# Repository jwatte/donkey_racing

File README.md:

Tools to help train the donkey car models.

`ip_beacon`: a program that broadcasts the presence of a node on a network for easy finding.
It can also browse for said nodes on the local network.

`teensy_rc_control`: a sketch for the Arduino IDE with the Teensyduino package installed, to 
control a gas-and-steering robot based on received RC commands and communication with a USB 
host (such as a Raspberry Pi or NVIDIA Jetson.)

`mktraining`: generates a synthetic set of images similar to what a rpi camera might capture.
horizontal FOV 60 degrees; resolution 320x240; random confetti on the floor for each image.
Libraries needed to build: GLFW and GLEW.

`blur`: blur a PNG image based on a mask given in another PNG image.

`teensy_32_carrier`: KiCad design files for the servo and receiver I/O board for the Teensy 3.2
microcontroller. Known flaws in revision 1.0:
  - Doesn't connect to Raspbery Pi "hat" port
  - Doesn't have enough I/Os to read BLDC motor sensors

All of these tools also want "stb" to be a checkout of github.com/nothings/stb as a peer 
to these directories.

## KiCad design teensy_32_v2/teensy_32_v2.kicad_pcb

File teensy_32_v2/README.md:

Teensy Hat notes

User manual: https://docs.google.com/document/d/1TIZRwT1liuum8qoM7WJbi-JH8VMrMioTwOWIgUCem8s/edit?usp=sharing

  * Version 1 (4 copies) commit number:  328d241c250156cd1f0e025fa5ad50edf611e549
  * Version 2 (8 copies) commit number:  3ad820124f71cb1f2d3cb137cd7d391197ac48be

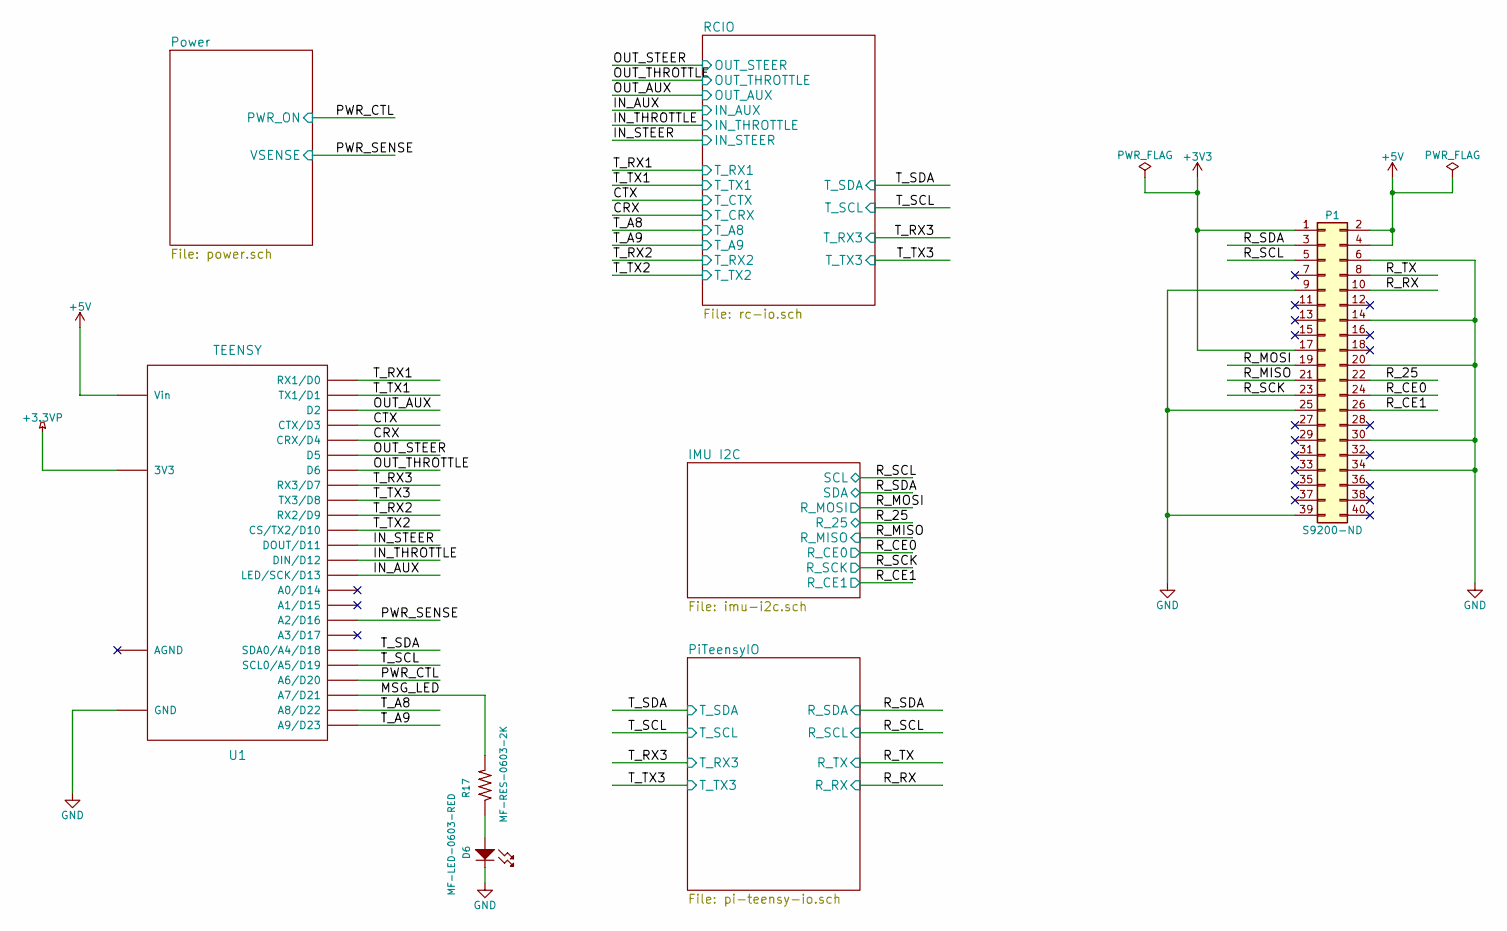
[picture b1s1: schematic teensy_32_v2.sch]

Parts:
D6: MF-LED-0603-RED; MF_LEDs-LED0603
P1: S9200-ND; RPI_BOTTOM_NOLABELS
R17: MF-RES-0603-2K; MF_Passives-R0603
U1: TEENSY; TEENSY_3

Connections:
+3.3VP: U1.26 (3V3)
+3V3: P1.1, P1.17; also elsewhere on the board
+5V: P1.2, P1.4, U1.28 (Vin); also elsewhere on the board
/CRX: U1.6 (CRX/D4); also elsewhere on the board
/CTX: U1.5 (CTX/D3); also elsewhere on the board
/IN_AUX: U1.15 (LED/SCK/D13); also elsewhere on the board
/IN_STEER: U1.13 (DOUT/D11); also elsewhere on the board
/IN_THROTTLE: U1.14 (DIN/D12); also elsewhere on the board
/MSG_LED: R17.2, U1.23 (A7/D21)
/OUT_AUX: U1.4 (D2); also elsewhere on the board
/OUT_STEER: U1.7 (D5); also elsewhere on the board
/OUT_THROTTLE: U1.8 (D6); also elsewhere on the board
/PWR_CTL: U1.22 (A6/D20); also elsewhere on the board
/PWR_SENSE: U1.18 (A2/D16); also elsewhere on the board
/R_25: P1.22; also elsewhere on the board
/R_CE0: P1.24; also elsewhere on the board
/R_CE1: P1.26; also elsewhere on the board
/R_MISO: P1.21; also elsewhere on the board
/R_MOSI: P1.19; also elsewhere on the board
/R_RX: P1.10; also elsewhere on the board
/R_SCK: P1.23; also elsewhere on the board
/R_SCL: P1.5; also elsewhere on the board
/R_SDA: P1.3; also elsewhere on the board
/R_TX: P1.8; also elsewhere on the board
/T_A8: U1.24 (A8/D22); also elsewhere on the board
/T_A9: U1.25 (A9/D23); also elsewhere on the board
/T_RX1: U1.2 (RX1/D0); also elsewhere on the board
/T_RX2: U1.11 (RX2/D9); also elsewhere on the board
/T_RX3: U1.9 (RX3/D7); also elsewhere on the board
/T_SCL: U1.21 (SCL0/A5/D19); also elsewhere on the board
/T_SDA: U1.20 (SDA0/A4/D18); also elsewhere on the board
/T_TX1: U1.3 (TX1/D1); also elsewhere on the board
/T_TX2: U1.12 (CS/TX2/D10); also elsewhere on the board
/T_TX3: U1.10 (TX3/D8); also elsewhere on the board
GND: D6.CATH (CATHODE), P1.6, P1.9, P1.14, P1.20, P1.25, P1.30, P1.34, P1.39, U1.1 (GND); also elsewhere on the board
unnamed: D6.ANOD (ANODE), R17.1

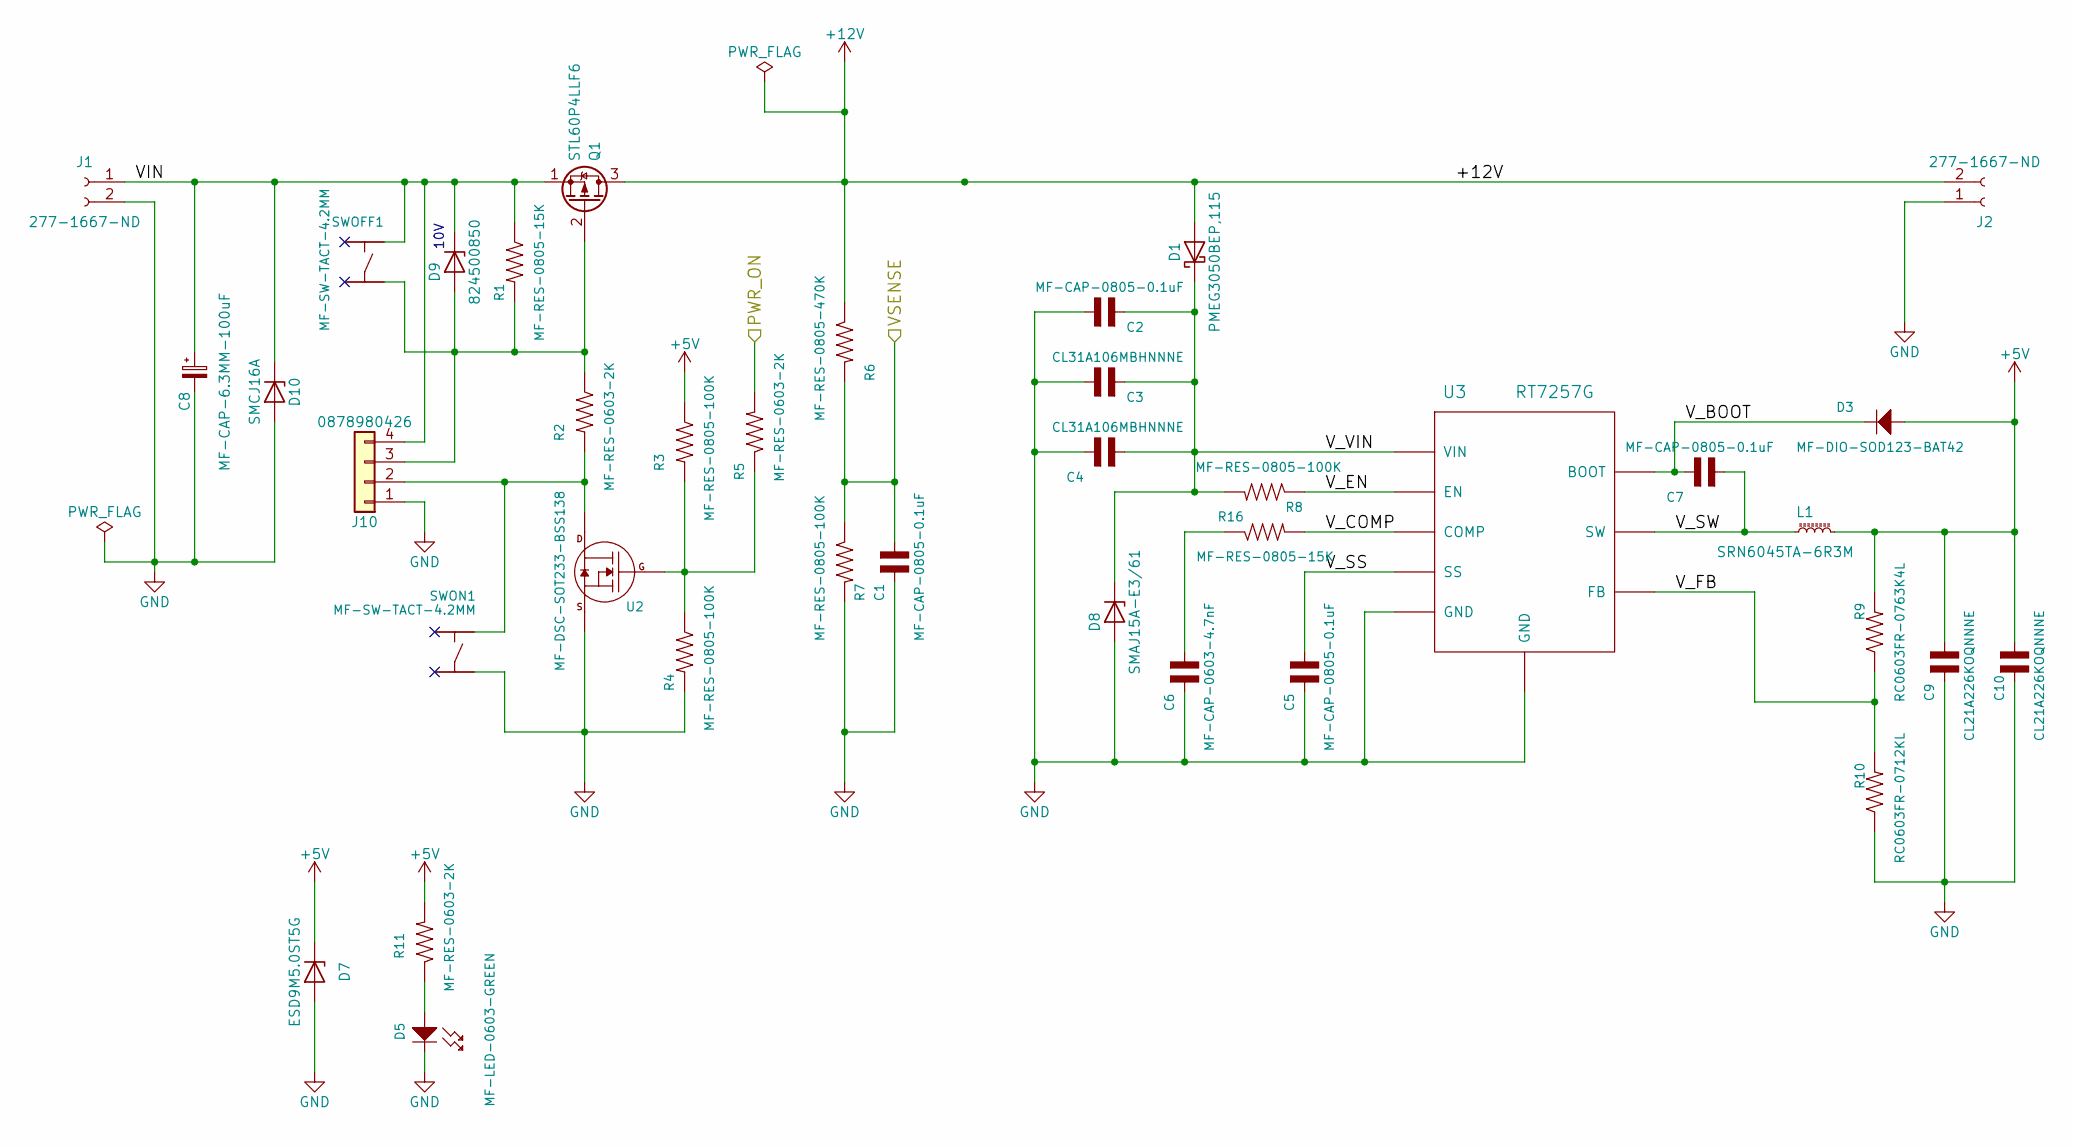
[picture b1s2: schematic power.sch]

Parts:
C1, C2, C5, C7: MF-CAP-0805-0.1uF; MF_Passives-C0805
C3, C4: CL31A106MBHNNNE; MF_Passives-C1206
C6: MF-CAP-0603-4.7nF; MF_Passives-C0603
C8: MF-CAP-6.3MM-100uF; MF_Passives-CP6.3MM
C9, C10: CL21A226KOQNNNE; MF_Passives-C0805
D1: PMEG3050BEP,115; SOD-128
D3: MF-DIO-SOD123-BAT42; MF_Discrete_Semiconductor-SOD-123
D5: MF-LED-0603-GREEN; MF_LEDs-LED0603
D7: ESD9M5.0ST5G; SOD-923
D8: SMAJ15A-E3/61; D_SMA_Standard
D9: 824500850; D_SMA_Standard
D10: SMCJ16A; D_SMC_Standard
J1, J2: 277-1667-ND; PhoenixContact_MCV-G_02x5.08mm_Vertical
J10: 0878980426; MF_Connectors-PTH_2.54MM_01X04
L1: SRN6045TA-6R3M; SRN6045TA
Q1: STL60P4LLF6; POWERFLAT_5x6
R1, R16: MF-RES-0805-15K; MF_Passives-R0805
R2, R5, R11: MF-RES-0603-2K; MF_Passives-R0603
R3, R4, R7, R8: MF-RES-0805-100K; MF_Passives-R0805
R6: MF-RES-0805-470K; MF_Passives-R0805
R9: RC0603FR-0763K4L; MF_Passives-R0603
R10: RC0603FR-0712KL; MF_Passives-R0603
SWOFF1: MF-SW-TACT-4.2MM; MF_Switches-TACT4.2MM
SWON1: MF-SW-TACT-4.2MM; MF_Switches-TACT4.2MM
U2: MF-DSC-SOT233-BSS138; MF_Discrete_Semiconductor-SOT-23-3
U3: RT7257G; DS7257G

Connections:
+5V: C9.1, C10.1, D3.ANOD (ANODE), D7.1, L1.2, R3.1, R9.2, R11.2; also elsewhere on the board
+12V: D1.2 (A), J2.2, Q1.3 (D), R6.1; also elsewhere on the board
/PWR_CTL: R5.2; also elsewhere on the board
/PWR_SENSE: C1.1, R6.2, R7.1; also elsewhere on the board
/Power/VIN: C8.1, D9.1, D10.1 (K), J1.1, J10.4, Q1.1 (S), R1.1, SWOFF1.1
/Power/V_BOOT: C7.1, D3.CATH (CATHODE), U3.1 (BOOT)
/Power/V_COMP: R16.2, U3.6 (COMP)
/Power/V_EN: R8.1, U3.7 (EN)
/Power/V_FB: R9.1, R10.2, U3.5 (FB)
/Power/V_SS: C5.1, U3.8 (SS)
/Power/V_SW: C7.2, L1.1, U3.3 (SW)
/Power/V_VIN: C2.2, C3.2, C4.2, D1.1 (K), D8.1, R8.2, U3.2 (VIN)
GND: C1.2, C2.1, C3.1, C4.1, C5.2, C6.2, C8.2, C9.2, C10.2, D5.CATH (CATHODE), D7.2, D8.2, D10.2 (A), J1.2, J2.1, J10.1, R4.2, R7.2, R10.1, SWON1.3, U2.2 (SOURCE), U3.4 (GND), U3.9 (GND); also elsewhere on the board
unnamed: C6.1, R16.1
unnamed: D5.ANOD (ANODE), R11.1
unnamed: D9.2, J10.3, Q1.2 (G), R1.2, R2.1, SWOFF1.3
unnamed: J10.2, R2.2, SWON1.1, U2.3 (DRAIN)
unnamed: R3.2, R4.1, R5.1, U2.1 (GATE)

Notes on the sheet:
10V

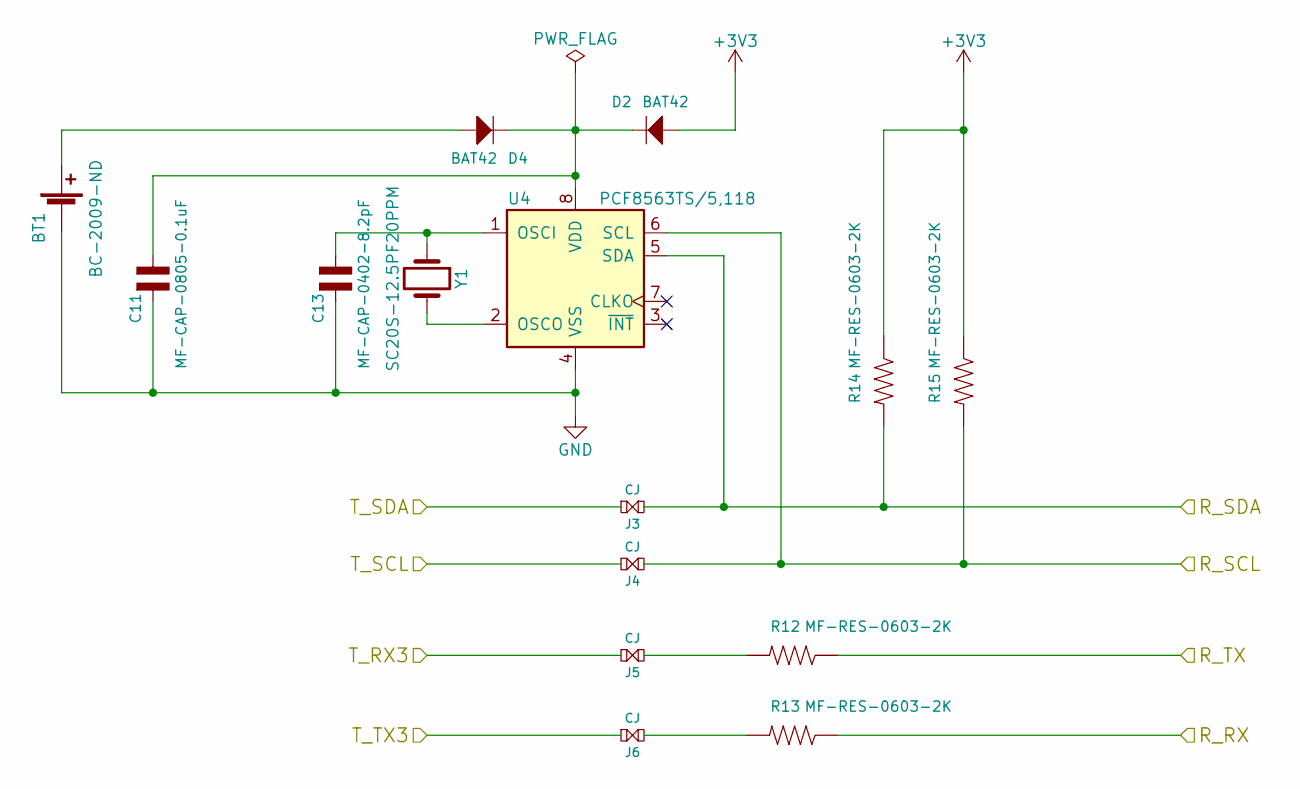
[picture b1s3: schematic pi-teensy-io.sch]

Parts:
BT1: BC-2009-ND
C11: MF-CAP-0805-0.1uF; MF_Passives-C0805
C13: MF-CAP-0402-8.2pF; MF_Passives-C0402
D2, D4: BAT42; MF_Discrete_Semiconductor-SOD-123
J3, J4, J5, J6: CJ; CJ-2
R12, R13, R14, R15: MF-RES-0603-2K; MF_Passives-R0603
U4: PCF8563TS/5,118; TSSOP-8_3x3mm_Pitch0.65mm
Y1: SC20S-12.5PF20PPM; SC-20S

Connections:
+3V3: D2.ANOD (ANODE), R14.1, R15.1; also elsewhere on the board
/R_RX: R13.1; also elsewhere on the board
/R_SCL: J4.2, R15.2, U4.6 (SCL); also elsewhere on the board
/R_SDA: J3.2, R14.2, U4.5 (SDA); also elsewhere on the board
/R_TX: R12.1; also elsewhere on the board
/T_RX3: J5.1; also elsewhere on the board
/T_SCL: J4.1; also elsewhere on the board
/T_SDA: J3.1; also elsewhere on the board
/T_TX3: J6.1; also elsewhere on the board
GND: BT1.2 (-), C11.2, C13.2, U4.4 (VSS); also elsewhere on the board
unnamed: BT1.1 (+), D4.ANOD (ANODE)
unnamed: C11.1, D2.CATH (CATHODE), D4.CATH (CATHODE), U4.8 (VDD)
unnamed: C13.1, U4.1 (OSCI), Y1.1
unnamed: J5.2, R12.2
unnamed: J6.2, R13.2
unnamed: U4.2 (OSCO), Y1.2

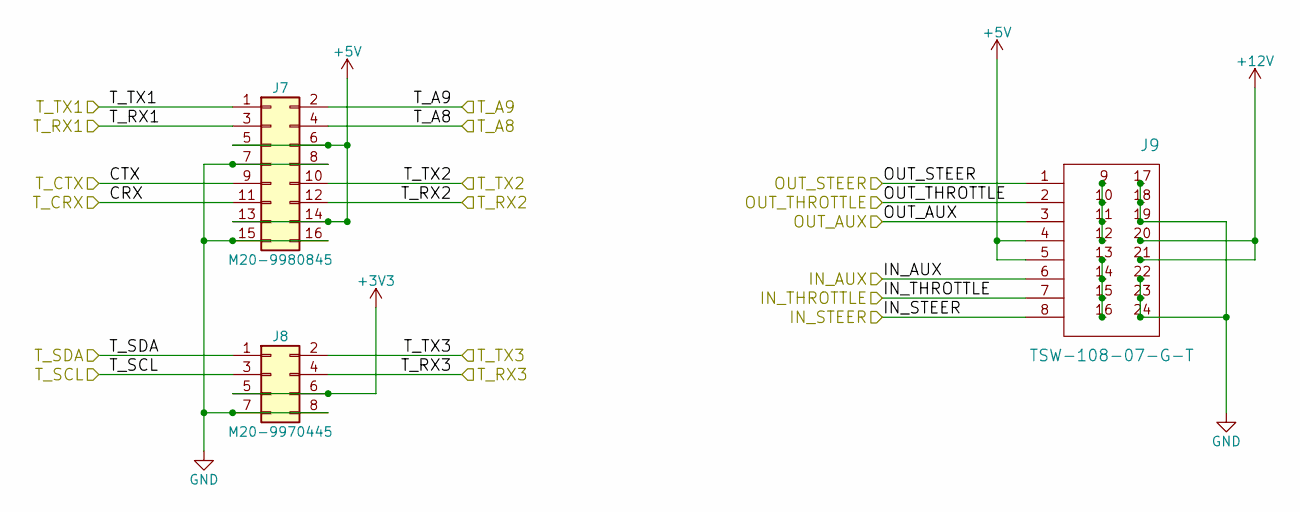
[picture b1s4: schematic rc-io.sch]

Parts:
J7: M20-9980845; Pin_Header_Straight_2x08_Pitch2.54mm
J8: M20-9970445; Pin_Header_Straight_2x04_Pitch2.54mm
J9: TSW-108-07-G-T; CONN_03x08

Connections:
+3V3: J8.5, J8.6; also elsewhere on the board
+5V: J7.5, J7.6, J7.13, J7.14, J9.4, J9.5; also elsewhere on the board
+12V: J9.20, J9.21; also elsewhere on the board
/CRX: J7.11; also elsewhere on the board
/CTX: J7.9; also elsewhere on the board
/IN_AUX: J9.6; also elsewhere on the board
/IN_STEER: J9.8; also elsewhere on the board
/IN_THROTTLE: J9.7; also elsewhere on the board
/OUT_AUX: J9.3; also elsewhere on the board
/OUT_STEER: J9.1; also elsewhere on the board
/OUT_THROTTLE: J9.2; also elsewhere on the board
/T_A8: J7.4; also elsewhere on the board
/T_A9: J7.2; also elsewhere on the board
/T_RX1: J7.3; also elsewhere on the board
/T_RX2: J7.12; also elsewhere on the board
/T_RX3: J8.4; also elsewhere on the board
/T_SCL: J8.3; also elsewhere on the board
/T_SDA: J8.1; also elsewhere on the board
/T_TX1: J7.1; also elsewhere on the board
/T_TX2: J7.10; also elsewhere on the board
/T_TX3: J8.2; also elsewhere on the board
GND: J7.7, J7.8, J7.15, J7.16, J8.7, J8.8, J9.17, J9.18, J9.19, J9.22, J9.23, J9.24; also elsewhere on the board
unnamed: J9.9, J9.10, J9.11, J9.12
unnamed: J9.13, J9.14, J9.15, J9.16

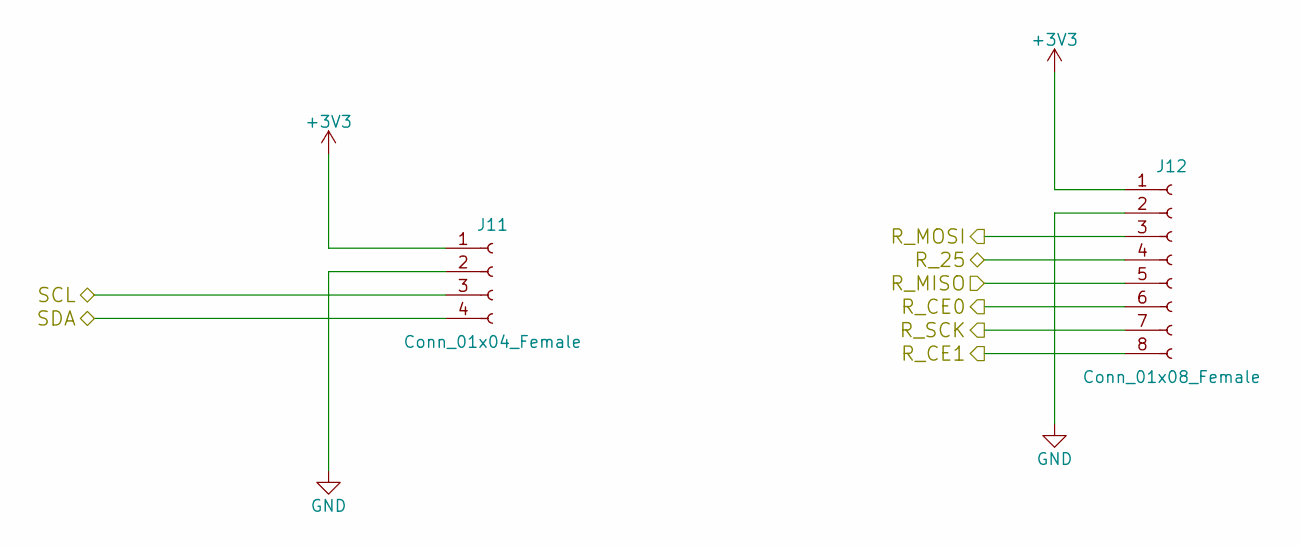
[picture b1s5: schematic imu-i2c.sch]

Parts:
J11: Conn_01x04_Female; Pin_Header_Straight_1x04_Pitch2.54mm
J12: Conn_01x08_Female; Pin_Header_Straight_1x08_Pitch2.54mm

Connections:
+3V3: J11.1, J12.1; also elsewhere on the board
/R_25: J12.4; also elsewhere on the board
/R_CE0: J12.6; also elsewhere on the board
/R_CE1: J12.8; also elsewhere on the board
/R_MISO: J12.5; also elsewhere on the board
/R_MOSI: J12.3; also elsewhere on the board
/R_SCK: J12.7; also elsewhere on the board
/R_SCL: J11.3; also elsewhere on the board
/R_SDA: J11.4; also elsewhere on the board
GND: J11.2, J12.2; also elsewhere on the board

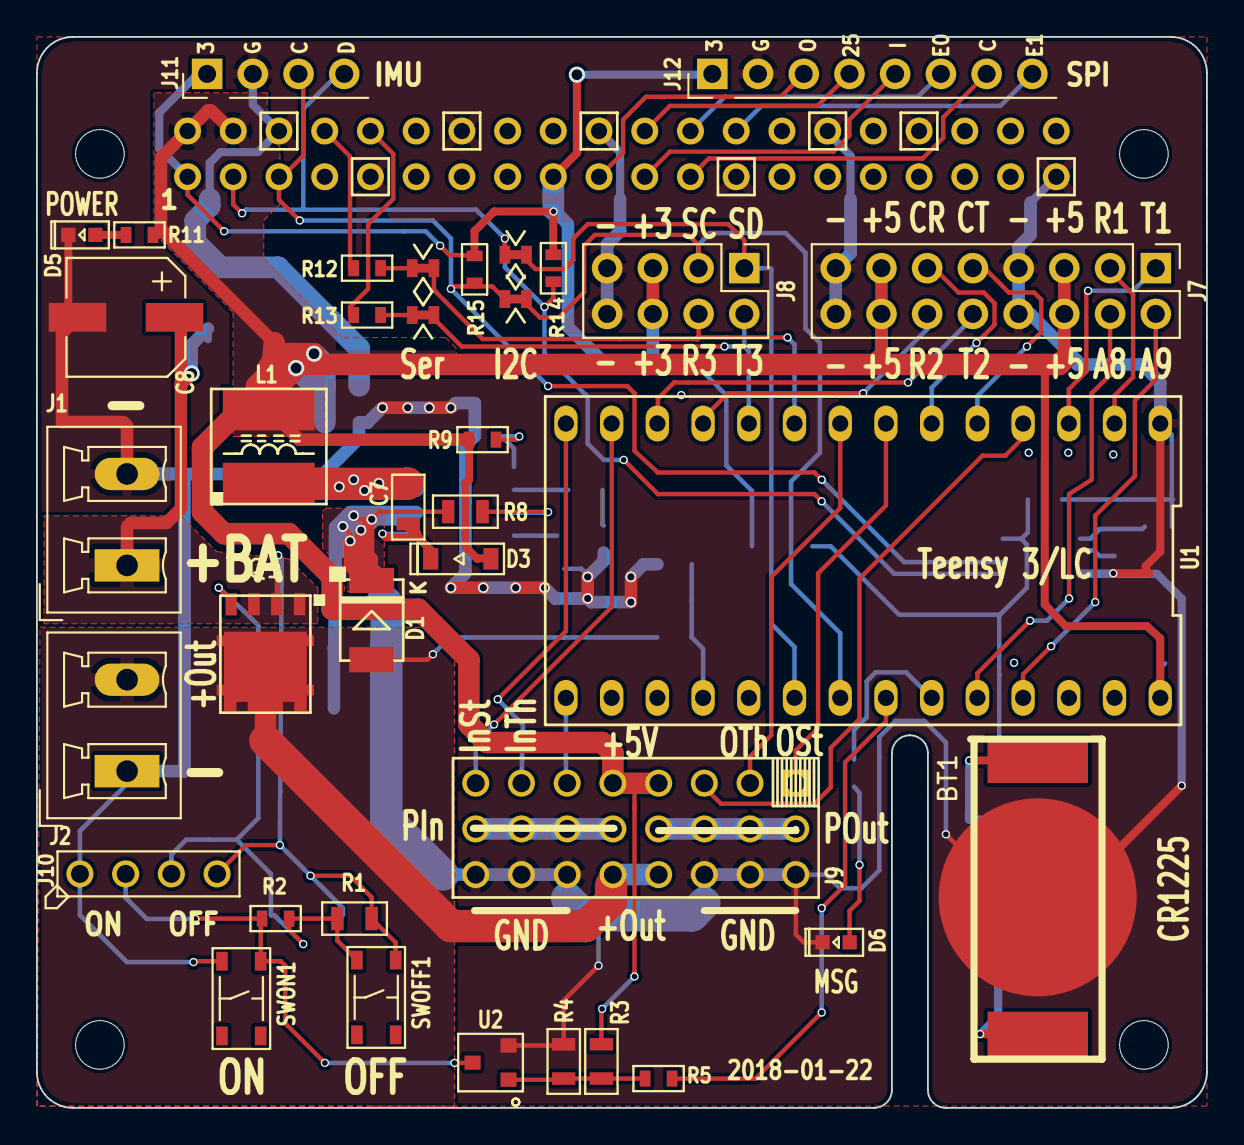
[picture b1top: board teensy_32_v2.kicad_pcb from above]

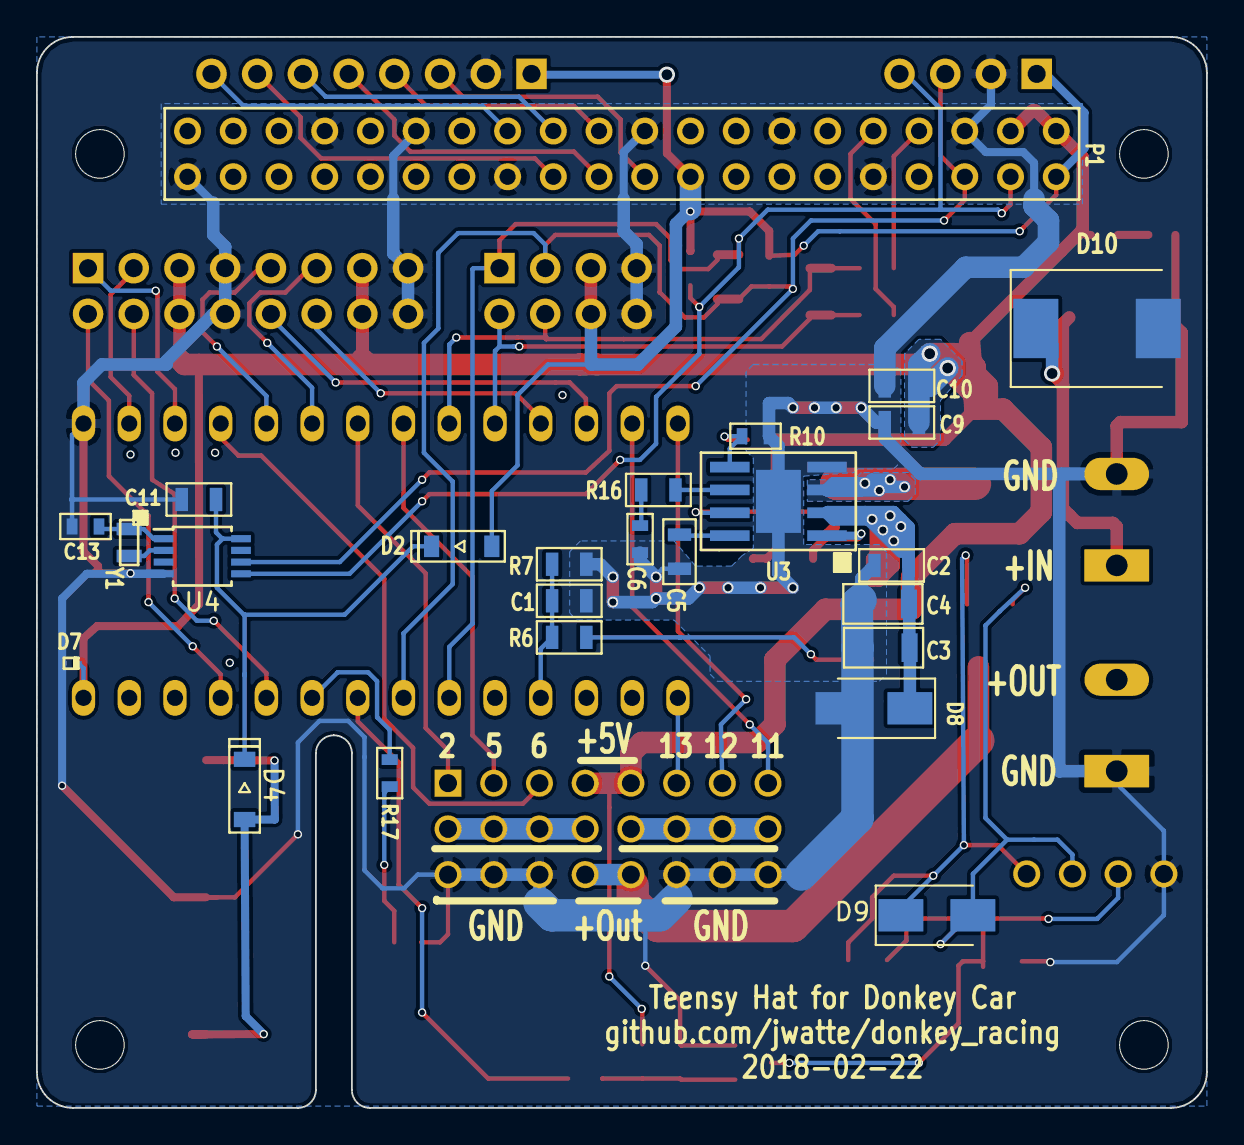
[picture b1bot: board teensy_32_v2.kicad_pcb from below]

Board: 2 copper layers, 65.0 x 59.5 mm, 62 parts (25 on the bottom side), 57 nets.

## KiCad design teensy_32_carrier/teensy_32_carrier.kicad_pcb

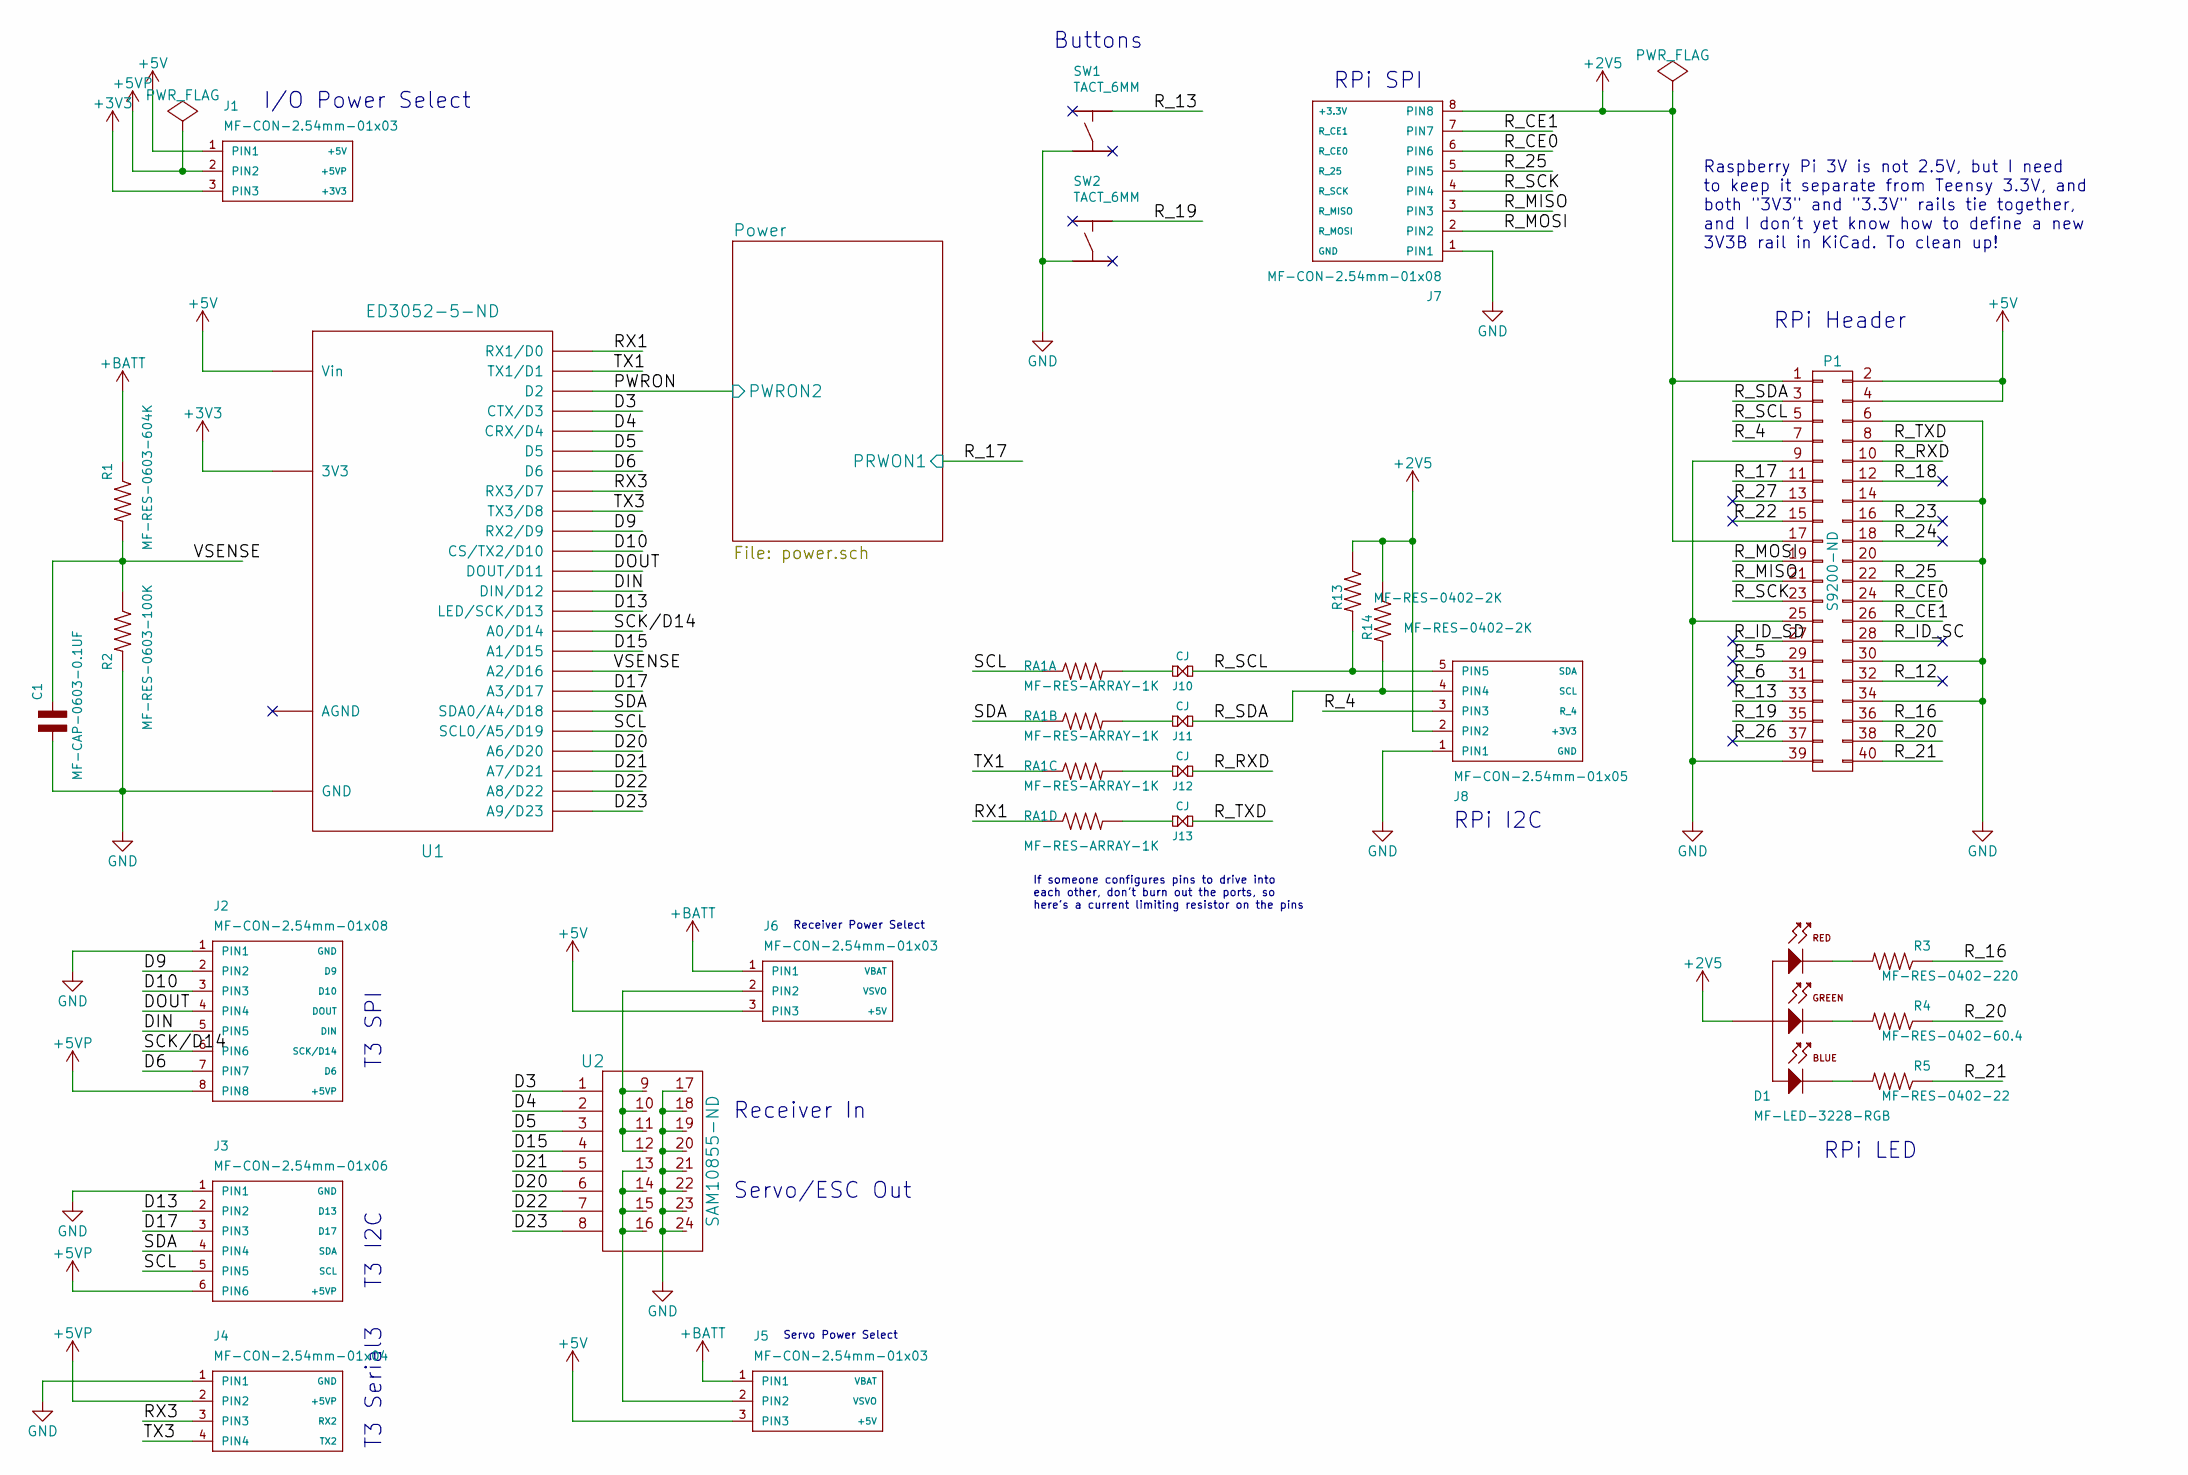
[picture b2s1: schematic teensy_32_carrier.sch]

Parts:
C1: MF-CAP-0603-0.1UF; MF_Passives-C0603
D1: MF-LED-3228-RGB; MF_LEDs-PLCC4
J1, J5, J6: MF-CON-2.54mm-01x03; MF_Connectors-PTH_2.54MM_01X03
J2, J7: MF-CON-2.54mm-01x08; MF_Connectors-PTH_2.54MM_01X08
J3: MF-CON-2.54mm-01x06; MF_Connectors-PTH_2.54MM_01X06
J4: MF-CON-2.54mm-01x04; MF_Connectors-PTH_2.54MM_01X04
J8: MF-CON-2.54mm-01x05; MF_Connectors-PTH_2.54MM_01X05
J10, J11, J12, J13: CJ; CJ-2
P1: S9200-ND; RPI_BOTTOM_NOLABELS
R1: MF-RES-0603-604K; MF_Passives-R0603
R2: MF-RES-0603-100K; MF_Passives-R0603
R3: MF-RES-0402-220; MF_Passives-R0402
R4: MF-RES-0402-60.4; MF_Passives-R0402
R5: MF-RES-0402-22; MF_Passives-R0402
R13, R14: MF-RES-0402-2K; MF_Passives-R0402
RA1: MF-RES-ARRAY-1K; MF_Passives-RA1206
SW1, SW2: TACT_6MM; MF_Switches-TACT6MM
U1: ED3052-5-ND; TEENSY_3
U2: SAM10855-ND; CONN_03x08

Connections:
+2V5: D1.1 (ANODE), J7.8 (PIN8), J8.2 (PIN2), P1.1, P1.17, R13.1, R14.1
+3V3: J1.3 (PIN3), U1.26 (3V3)
+5V: J1.1 (PIN1), J5.3 (PIN3), J6.3 (PIN3), P1.2, P1.4, U1.28 (Vin); also elsewhere on the board
+5VP: J1.2 (PIN2), J2.8 (PIN8), J3.6 (PIN6), J4.2 (PIN2)
+BATT: J5.1 (PIN1), J6.1 (PIN1), R1.1; also elsewhere on the board
/D3: U1.5 (CTX/D3), U2.1
/D4: U1.6 (CRX/D4), U2.2
/D5: U1.7 (D5), U2.3
/D6: J2.7 (PIN7), U1.8 (D6)
/D9: J2.2 (PIN2), U1.11 (RX2/D9)
/D10: J2.3 (PIN3), U1.12 (CS/TX2/D10)
/D13: J3.2 (PIN2), U1.15 (LED/SCK/D13)
/D15: U1.17 (A1/D15), U2.4
/D17: J3.3 (PIN3), U1.19 (A3/D17)
/D20: U1.22 (A6/D20), U2.6
/D21: U1.23 (A7/D21), U2.5
/D22: U1.24 (A8/D22), U2.7
/D23: U1.25 (A9/D23), U2.8
/DIN: J2.5 (PIN5), U1.14 (DIN/D12)
/DOUT: J2.4 (PIN4), U1.13 (DOUT/D11)
/PWRON: U1.4 (D2); also elsewhere on the board
/RX1: RA1.4 (1), U1.2 (RX1/D0)
/RX3: J4.3 (PIN3), U1.9 (RX3/D7)
/R_4: J8.3 (PIN3), P1.7
/R_5: P1.29
/R_6: P1.31
/R_12: P1.32
/R_13: P1.33, SW1.2
/R_16: P1.36, R3.1
/R_17: P1.11; also elsewhere on the board
/R_18: P1.12
/R_19: P1.35, SW2.2
/R_20: P1.38, R4.1
/R_21: P1.40, R5.1
/R_22: P1.15
/R_23: P1.16
/R_24: P1.18
/R_25: J7.5 (PIN5), P1.22
/R_26: P1.37
/R_27: P1.13
/R_CE0: J7.6 (PIN6), P1.24
/R_CE1: J7.7 (PIN7), P1.26
/R_ID_SC: P1.28
/R_ID_SD: P1.27
/R_MISO: J7.3 (PIN3), P1.21
/R_MOSI: J7.2 (PIN2), P1.19
/R_RXD: J12.2, P1.10
/R_SCK: J7.4 (PIN4), P1.23
/R_SCL: J8.5 (PIN5), J10.2, P1.5, R13.2
/R_SDA: J8.4 (PIN4), J11.2, P1.3, R14.2
/R_TXD: J13.2, P1.8
/SCK/D14: J2.6 (PIN6), U1.16 (A0/D14)
/SCL: J3.5 (PIN5), RA1.1, U1.21 (SCL0/A5/D19)
/SDA: J3.4 (PIN4), RA1.2 (1), U1.20 (SDA0/A4/D18)
/TX1: RA1.3 (1), U1.3 (TX1/D1)
/TX3: J4.4 (PIN4), U1.10 (TX3/D8)
/VSENSE: C1.1, R1.2, R2.1, U1.18 (A2/D16)
GND: C1.2, J2.1 (PIN1), J3.1 (PIN1), J4.1 (PIN1), J7.1 (PIN1), J8.1 (PIN1), P1.6, P1.9, P1.14, P1.20, P1.25, P1.30, P1.34, P1.39, R2.2, SW1.3, SW2.3, U1.1 (GND), U2.17, U2.18, U2.19, U2.20, U2.21, U2.22, U2.23, U2.24; also elsewhere on the board
unnamed: D1.2 (CATHODE_RED), R3.2
unnamed: D1.3 (CATHODE_GREEN), R4.2
unnamed: D1.4 (CATHODE_BLUE), R5.2
unnamed: J5.2 (PIN2), U2.13, U2.14, U2.15, U2.16
unnamed: J6.2 (PIN2), U2.9, U2.10, U2.11, U2.12
unnamed: J10.1, RA1.8 (2)
unnamed: J11.1, RA1.7 (2)
unnamed: J12.1, RA1.6 (2)
unnamed: J13.1, RA1.5 (2)

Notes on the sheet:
Receiver In
Servo/ESC Out
Servo Power Select
Receiver Power Select
I/O Power Select
T3 SPI
T3 I2C
T3 Serial3
Buttons
RPi SPI
RPi I2C
RPi LED
RPi Header
Raspberry Pi 3V is not 2.5V, but I need to keep it separate from Teensy 3.3V, and both "3V3" and "3.3V" rails tie together, and I don't yet know how to define a new 3V3B rail in KiCad. To clean up!
If someone configures pins to drive into each other, don't burn out the ports, so here's a current limiting resistor on the pins

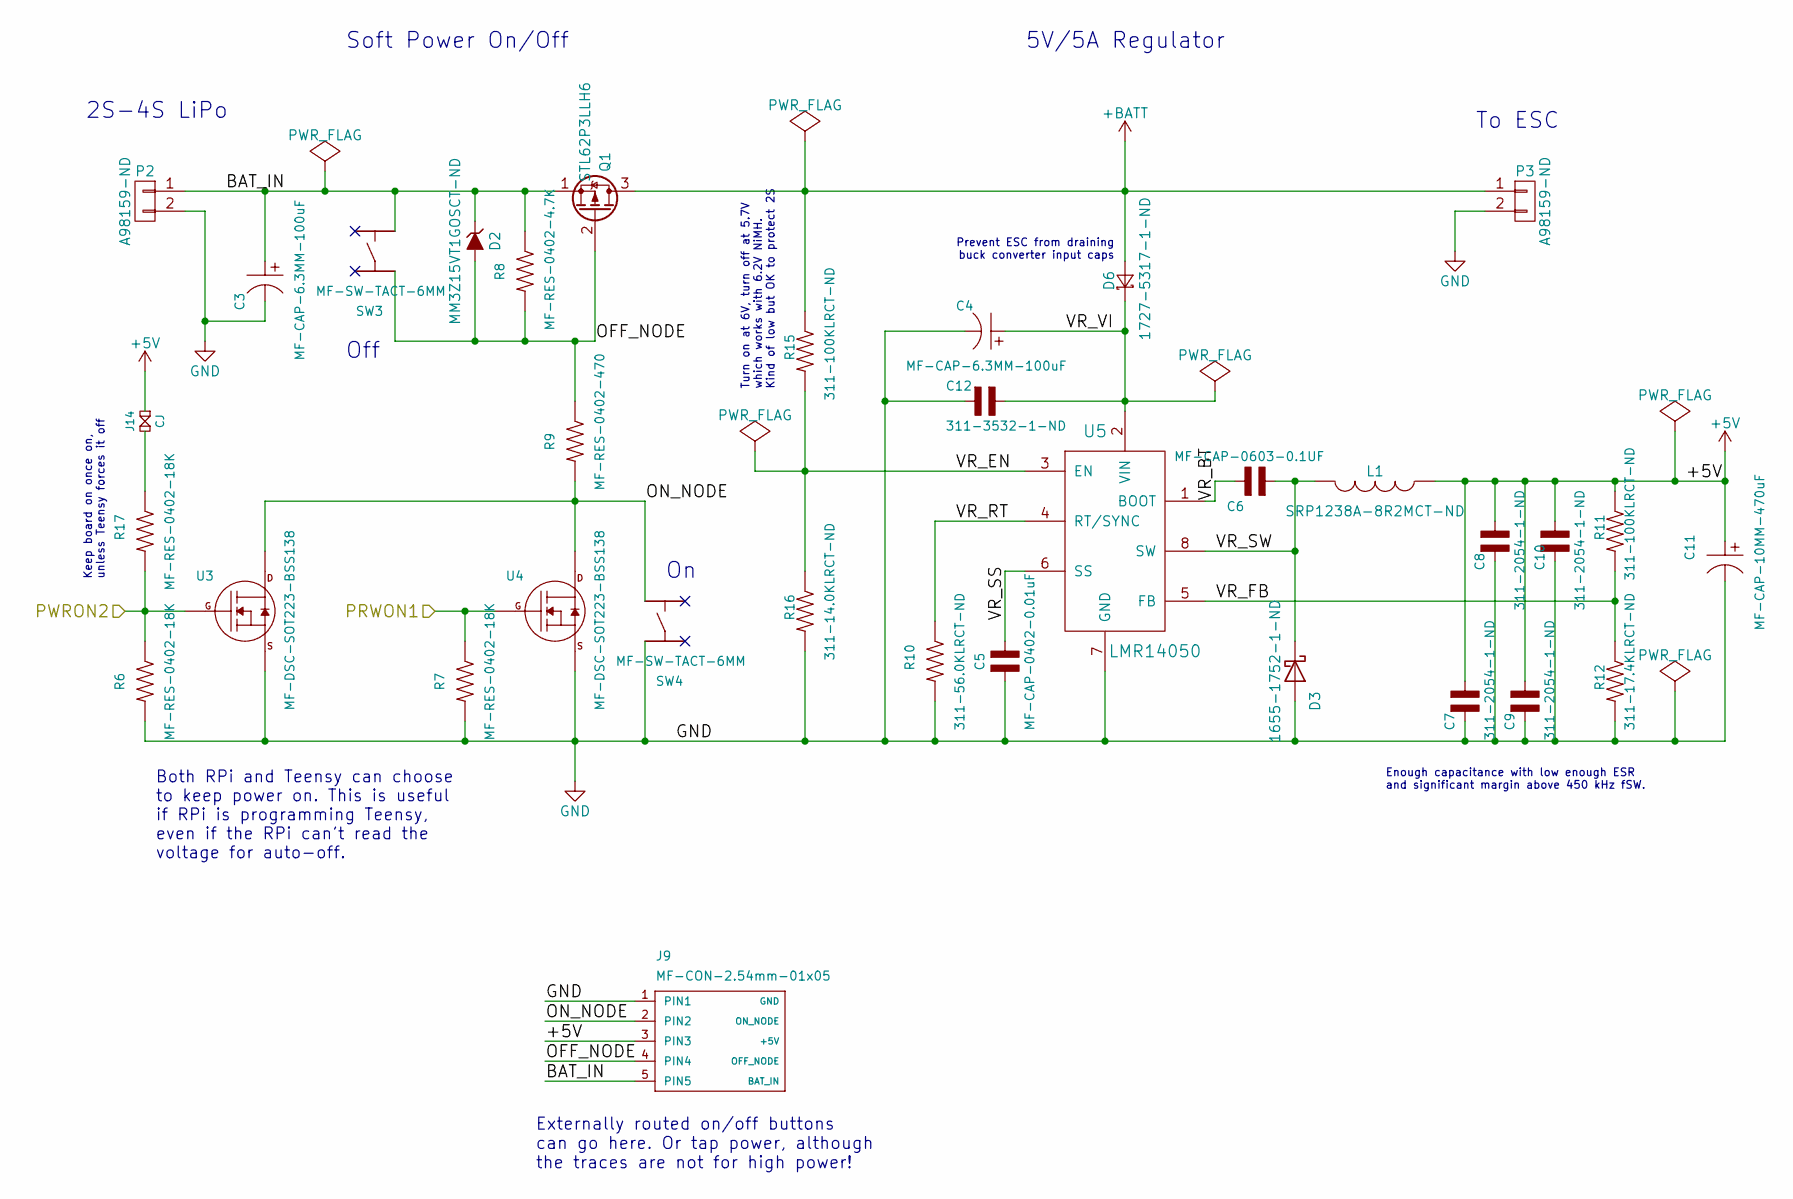
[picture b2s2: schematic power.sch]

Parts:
C3, C4: MF-CAP-6.3MM-100uF; MF_Passives-CP6.3MM
C5: MF-CAP-0402-0.01uF; MF_Passives-C0402
C6: MF-CAP-0603-0.1UF; MF_Passives-C0603
C7, C8, C9, C10: 311-2054-1-ND; MF_Passives-C1210
C11: MF-CAP-10MM-470uF; MF_Passives-CP10MM
C12: 311-3532-1-ND; MF_Passives-C1210
D2: MM3Z15VT1GOSCT-ND; SOD-323
D3: 1655-1752-1-ND; TO-277B
D6: 1727-5317-1-ND; SOD-128
J9: MF-CON-2.54mm-01x05; MF_Connectors-PTH_2.54MM_01X05
J14: CJ; CJ-2
L1: SRP1238A-8R2MCT-ND; BOURNS_SRP1238A
P2, P3: A98159-ND; SCREW-3.5MM
Q1: STL62P3LLH6; POWERFLAT_5x6
R6, R7, R17: MF-RES-0402-18K; MF_Passives-R0402
R8: MF-RES-0402-4.7K; MF_Passives-R0402
R9: MF-RES-0402-470; MF_Passives-R0402
R10: 311-56.0KLRCT-ND; MF_Passives-R0402
R11, R15: 311-100KLRCT-ND; MF_Passives-R0402
R12: 311-17.4KLRCT-ND; MF_Passives-R0402
R16: 311-14.0KLRCT-ND; MF_Passives-R0402
SW3, SW4: MF-SW-TACT-6MM; MF_Switches-TACT6MM
U3, U4: MF-DSC-SOT223-BSS138; MF_Discrete_Semiconductor-SOT-23-3
U5: LMR14050; POWERPAD-8

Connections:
+5V: C7.1, C8.1, C9.1, C10.1, C11.1, J9.3 (PIN3), J14.1, L1.1, R11.1; also elsewhere on the board
+BATT: D6.2 (A), P3.1, Q1.3 (D), R15.1; also elsewhere on the board
/PWRON: R6.1, R17.2, U3.1 (GATE); also elsewhere on the board
/Power/BAT_IN: C3.1, D2.1 (K), J9.5 (PIN5), P2.1, Q1.1 (S), R8.1, SW3.2
/Power/OFF_NODE: D2.2 (A), J9.4 (PIN4), Q1.2 (G), R8.2, R9.1, SW3.4
/Power/ON_NODE: J9.2 (PIN2), R9.2, SW4.1, U3.3 (DRAIN), U4.3 (DRAIN)
/Power/VR_BT: C6.1, U5.1 (BOOT)
/Power/VR_EN: R15.2, R16.1, U5.3 (EN)
/Power/VR_FB: R11.2, R12.1, U5.5 (FB)
/Power/VR_RT: R10.1, U5.4 (RT/SYNC)
/Power/VR_SS: C5.1, U5.6 (SS)
/Power/VR_SW: C6.2, D3.1 (K), L1.2, U5.8 (SW)
/Power/VR_VI: C4.1, C12.1, D6.1 (K), U5.2 (VIN)
/R_17: R7.1, U4.1 (GATE); also elsewhere on the board
GND: C3.2, C4.2, C5.2, C7.2, C8.2, C9.2, C10.2, C11.2, C12.2, D3.2 (A), J9.1 (PIN1), P2.2, P3.2, R6.2, R7.2, R10.2, R12.2, R16.2, SW4.3, U3.2 (SOURCE), U4.2 (SOURCE), U5.7 (GND); also elsewhere on the board
unnamed: J14.2, R17.1

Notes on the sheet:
5V/5A Regulator
Soft Power On/Off
To ESC
2S-4S LiPo
Both RPi and Teensy can choose to keep power on. This is useful if RPi is programming Teensy, even if the RPi can't read the voltage for auto-off.
Off
Turn on at 6V, turn off at 5.7V which works with 6.2V NiMH. Kind of low but OK to protect 2S
Enough capacitance with low enough ESR and significant margin above 450 kHz fSW.
Prevent ESC from draining buck converter input caps
Keep board on once on, unless Teensy forces it off
Externally routed on/off buttons can go here. Or tap power, although the traces are not for high power!
